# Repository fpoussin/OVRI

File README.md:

# OVRI
Open source/hardware MCU based VR Sensor interface

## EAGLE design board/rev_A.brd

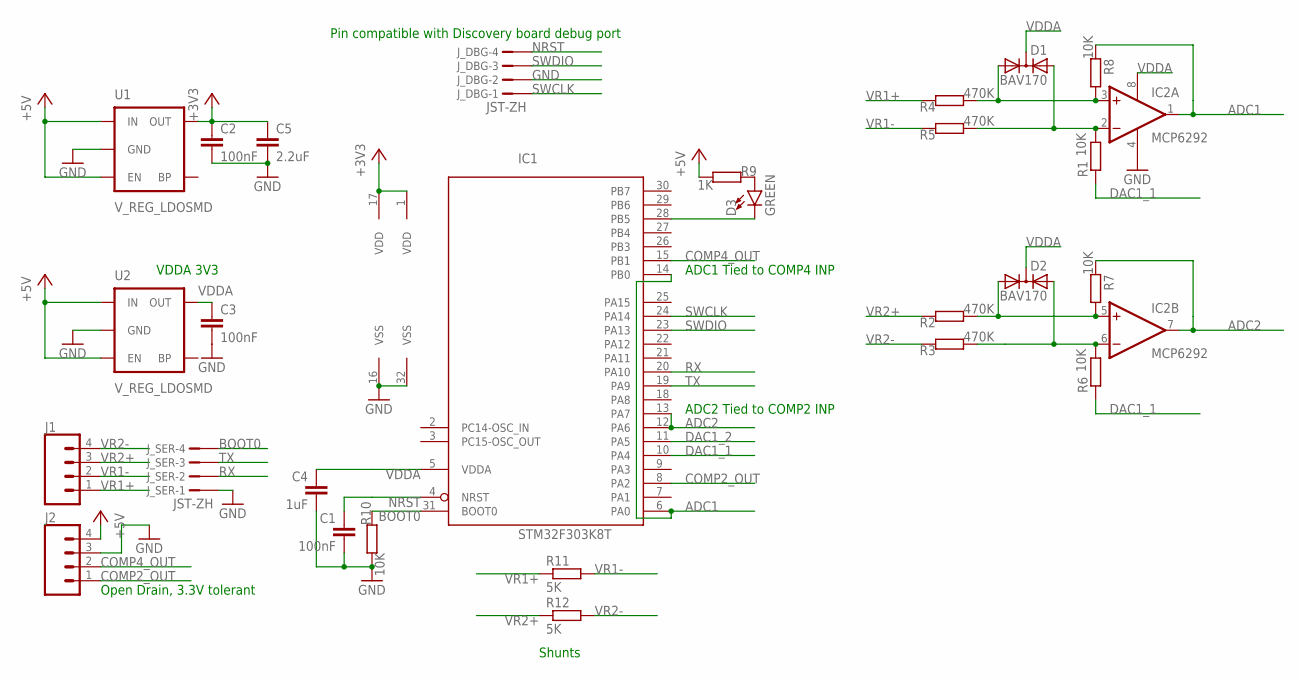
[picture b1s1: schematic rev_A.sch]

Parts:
C1, C2, C3: 100nF; C0603
C4: 1uF; C0603
C5: 2.2uF; C0603
D1, D2: BAV170; SOT23
D3: GREEN; LED-0603
IC1: STM32F303K8T; LQFP32
IC2: MCP6292; SO08
J1, J2: CONN_04LOCK; 1X04_LOCK
J_DBG: JST-ZH; B4B-ZR
J_SER: JST-ZH; B4B-ZR
R1, R6, R7, R8, R10: 10K; R0603
R2, R3, R4, R5: 470K; R0603
R9: 1K; R0603
R11, R12: 5K; 0411/12
U1, U2: V_REG_LDOSMD; SOT23-5

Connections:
+3V3: C2.1, C5.1, IC1.1 (VDD), IC1.17 (VDD), U1.5 (OUT)
+5V: J2.4, R9.2, U1.1 (IN), U1.3 (EN), U2.1 (IN), U2.3 (EN)
ADC1: IC1.6 (PA0), IC1.14 (PB0), IC2.1 (OUT), R8.2
ADC2: IC1.12 (PA6), IC1.13 (PA7), IC2.7 (OUT), R7.2
BOOT0: IC1.31 (BOOT0), J_SER.4, R10.1
COMP2_OUT: IC1.8 (PA2), J2.1
COMP4_OUT: IC1.15 (PB1), J2.2
DAC1_1: IC1.10 (PA4), R1.1, R6.1
DAC1_2: IC1.11 (PA5)
GND: C1.2, C2.2, C3.2, C4.2, C5.2, IC1.16 (VSS), IC1.32 (VSS), IC2.4 (V-), J2.3, J_DBG.2, J_SER.1, R10.2, U1.2 (GND), U2.2 (GND)
unnamed: D2.1 (A1), IC2.5 (+IN), R2.2, R7.1
unnamed: D1.1 (A1), IC2.3 (+IN), R4.2, R8.1
unnamed: D3.C, IC1.28 (PB5)
unnamed: D3.A, R9.1
NRST: C1.1, IC1.4 (NRST), J_DBG.4
PEAK1: D1.2 (A2), IC2.2 (-IN), R1.2, R5.2
PEAK2: D2.2 (A2), IC2.6 (-IN), R3.2, R6.2
RX: IC1.20 (PA10), J_SER.2
SWCLK: IC1.24 (PA14), J_DBG.1
SWDIO: IC1.23 (PA13), J_DBG.3
TX: IC1.19 (PA9), J_SER.3
VDDA: C3.1, C4.1, D1.3 (C), D2.3 (C), IC1.5 (VDDA), IC2.8 (V+), U2.5 (OUT)
VR1+: J1.1, R4.1, R11.1
VR1-: J1.2, R5.1, R11.2
VR2+: J1.3, R2.1, R12.1
VR2-: J1.4, R3.1, R12.2

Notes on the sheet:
VDDA 3V3
ADC2 Tied to COMP2 INP
ADC1 Tied to COMP4 INP
Open Drain, 3.3V tolerant
Pin compatible with Discovery board debug port
Shunts

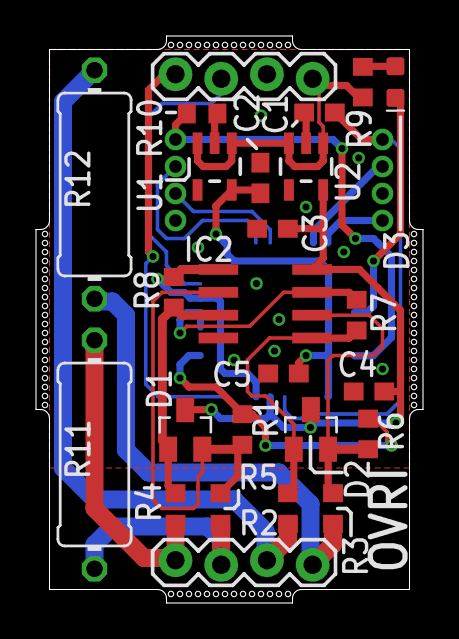
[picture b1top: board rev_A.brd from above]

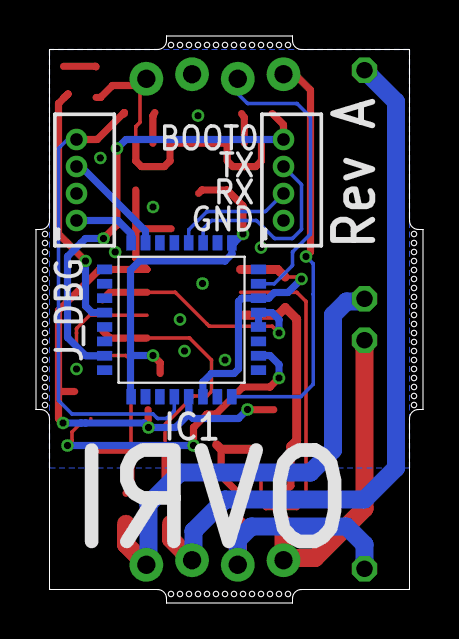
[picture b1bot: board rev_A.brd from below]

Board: 2 copper layers, 21.5 x 31.5 mm, 28 parts (3 on the bottom side), 25 nets.

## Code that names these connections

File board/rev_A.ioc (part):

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Mcu.Name=STM32F303K(6-8)Tx
Mcu.Package=LQFP32
Mcu.UserName=STM32F303K8Tx
PA0.Mode=IN1-Single-Ended
PA0.Signal=ADC1_IN1
PA10.Mode=Asynchronous
PA10.Signal=USART1_RX
PA13.Mode=Serial_Wire
PA13.Signal=SYS_JTMS-SWDIO
PA14.Mode=Serial_Wire
PA14.Signal=SYS_JTCK-SWCLK
PA2.Mode=ExternalOutput
PA2.Signal=COMP2_OUT
PA4.Signal=COMP_DAC11_group
PA5.Signal=COMP_DAC12_group
PA6.Mode=IN3-Single-Ended
PA6.Signal=ADC2_IN3
PA7.Mode=INP
PA7.Signal=COMP2_INP
PA9.Mode=Asynchronous
PA9.Signal=USART1_TX
PB0.Mode=INP
PB0.Signal=COMP4_INP
PB1.Mode=ExternalOutput
PB1.Signal=COMP4_OUT
PB4.Signal=S_TIM16_CH1
PB5.Signal=S_TIM17_CH1
RCC.HSEPLLFreq_Value=8000000
RCC.HSE_VALUE=8000000
RCC.SYSCLKFreq_VALUE=8000000

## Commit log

2017-02-05 [Board] Adding board files
2017-02-05 [Boards] Adding bypass cap and optimizing routing.
2017-02-05 [Code] Adding base code, gitignore file
2017-02-05 [Code] Cleanup
2017-02-05 [Code] Adding submodules
2017-02-05 [Code] Updating submodules
2017-02-06 [Board] Prepping for panels, cleaning labels, adding optional shunt resistors.
2017-02-06 [Code] Basic peripheral configs.
2017-02-13 [code] Updated submodules
2017-02-13 Cleaning submodules
2017-02-14 [code] Updating config files
2017-04-14 Updated ChibiOS submodule.

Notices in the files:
parts and their libraries:
SparkFun-LED: Licensing: Creative Commons ShareAlike 4.0 International - https://creativecommons.org/licenses/by-sa/4.0
SparkFun: Licensing: CC v3.0 Share-Alike You are welcome to use this library for commercial purposes.
